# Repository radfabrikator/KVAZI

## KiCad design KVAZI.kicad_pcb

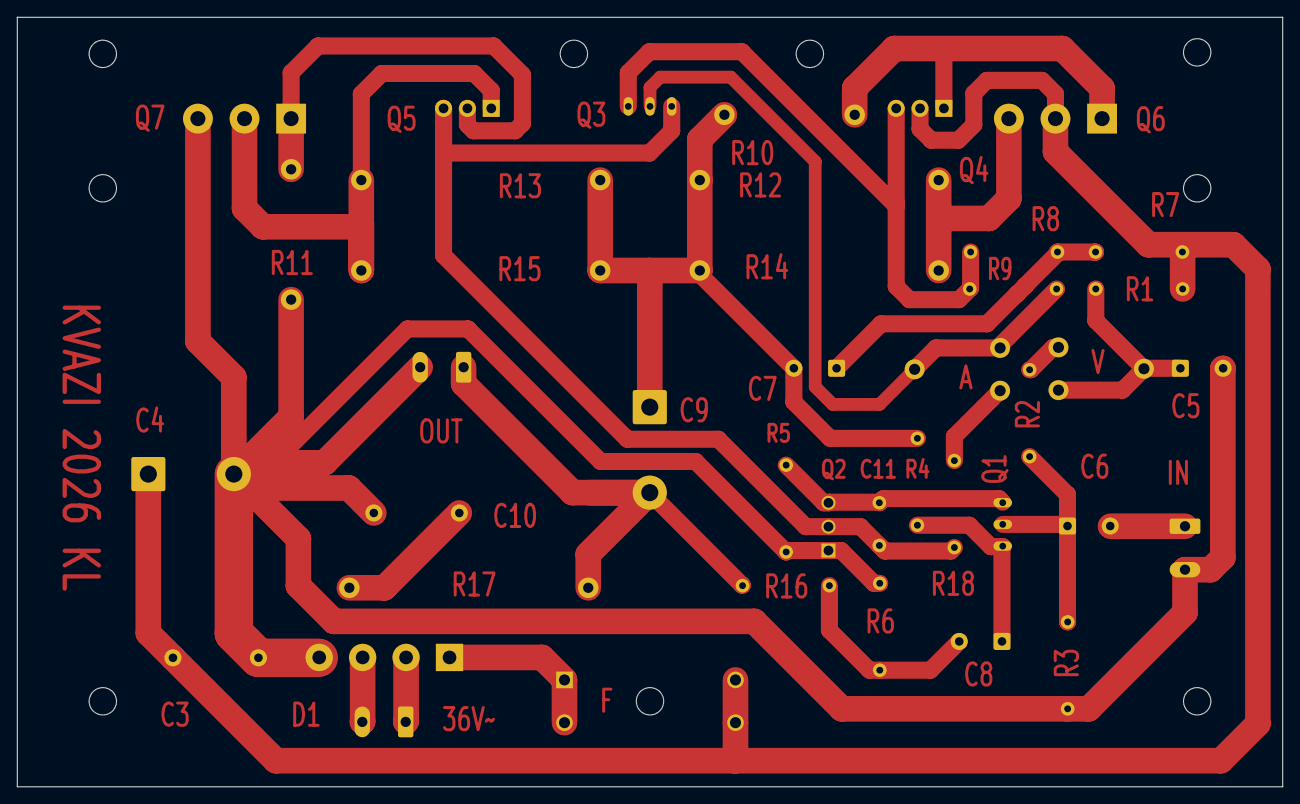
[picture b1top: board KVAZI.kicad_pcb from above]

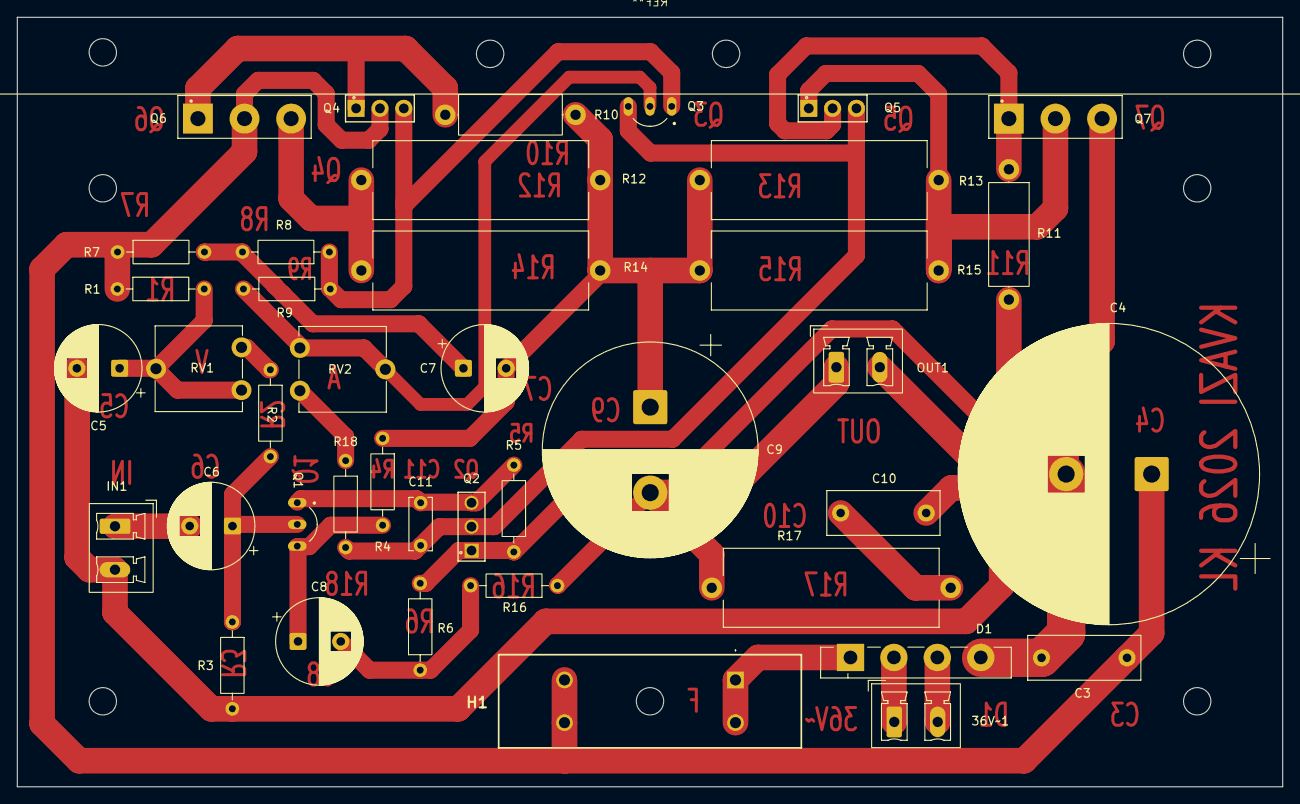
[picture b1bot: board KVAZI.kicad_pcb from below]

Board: 2 copper layers, 148.0 x 90.0 mm, 41 parts (41 on the bottom side), 24 nets.

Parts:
36V~1: Screw_Terminal_01x02; PhoenixContact_MCV_1,5_2-G-5.08_1x02_P5.08mm_Vertical
C3, C10: c=100n; C_Rect_L13.0mm_W5.0mm_P10.00mm_FKS3_FKP3_MKS4
C4: c=10000u; CP_Radial_D35.0mm_P10.00mm_SnapIn
C5: c=10u; CP_Radial_D10.0mm_P5.00mm
C6: c=2u; CP_Radial_D10.0mm_P5.00mm
C7: c=50u; CP_Radial_D10.0mm_P5.00mm
C8: c=100u; CP_Radial_D10.0mm_P5.00mm
C9: c=3300u; CP_Radial_D25.0mm_P10.00mm_SnapIn
C11: c=100p; C_Disc_D6.0mm_W2.5mm_P5.00mm
D1: GBU8D; Diode_Bridge_Vishay_GBU
H1: 0031.8231; 00318231
IN1: Screw_Terminal_01x02; PhoenixContact_MCV_1,5_2-G-5.08_1x02_P5.08mm_Vertical
OUT1: Screw_Terminal_01x02; PhoenixContact_MCV_1,5_2-G-5.08_1x02_P5.08mm_Vertical
Q1: BC556B; TO92254P460H750-3
Q2, Q4: BD139; SOT-32_STM
Q3: BC546B; TO92254P460H750-3
Q5: BD140; SOT-32_STM
Q6, Q7: TIP35C; TO545P1560X500X2445-3B
R1: r=82k; R_Axial_DIN0207_L6.3mm_D2.5mm_P10.16mm_Horizontal
R2: r=390k; R_Axial_DIN0207_L6.3mm_D2.5mm_P10.16mm_Horizontal
R3: r=470k; R_Axial_DIN0207_L6.3mm_D2.5mm_P10.16mm_Horizontal
R4, R16: r=10k; R_Axial_DIN0207_L6.3mm_D2.5mm_P10.16mm_Horizontal
R5: r=5.6k; R_Axial_DIN0207_L6.3mm_D2.5mm_P10.16mm_Horizontal
R6: r=91; R_Axial_DIN0207_L6.3mm_D2.5mm_P10.16mm_Horizontal
R7: r=330; R_Axial_DIN0207_L6.3mm_D2.5mm_P10.16mm_Horizontal
R8, R9: r=2.2k; R_Axial_DIN0207_L6.3mm_D2.5mm_P10.16mm_Horizontal
R10, R11: r=56; R_Axial_DIN0414_L11.9mm_D4.5mm_P15.24mm_Horizontal
R12, R13, R14, R15: r=1; R_Axial_Power_L25.0mm_W9.0mm_P27.94mm
R17: r=10; R_Axial_Power_L25.0mm_W9.0mm_P27.94mm
R18: r=1000; R_Axial_DIN0207_L6.3mm_D2.5mm_P10.16mm_Horizontal
RV1: 250k; Potentiometer_ACP_CA9-V10_Vertical
RV2: 1k; Potentiometer_ACP_CA9-V10_Vertical

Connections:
/U0: C7.2, C9.1, R4.1, R10.2, R12.2, R13.1, R14.2, R15.1
GND: C3.2, C4.2, C5.2, C10.2, D1.4 (-), IN1.2, OUT1.2, Q2.1 (E), Q7.3 (E), R3.2, R5.2, R6.2, R11.2
INPUT: C6.2, IN1.1
unnamed: 36V~1.1, D1.2
unnamed: 36V~1.2, D1.3
unnamed: C5.1, R1.2, RV1.2, RV1.3
unnamed: C7.1, R7.2, R8.2
unnamed: C8.2, R6.1, R16.2
unnamed: C10.1, R17.2
unnamed: D1.1 (+), H1.1, H1.2
unnamed: C6.1, Q1.2 (B), R2.2, R3.1
unnamed: C11.1, Q1.1 (C), Q2.3 (B), R5.1
unnamed: C8.1, Q1.3 (E), R4.2
unnamed: C11.2, Q2.2 (C), Q3.3 (E), Q5.3 (B), R18.2
unnamed: Q3.2 (B), R9.2, RV2.2, RV2.3
unnamed: Q3.1 (C), Q4.3 (B), R8.1, R9.1
unnamed: Q4.1 (E), Q6.1 (B), R10.1
unnamed: Q5.2 (C), Q7.1 (B), R11.1
unnamed: Q5.1 (E), Q7.2 (C), R13.2, R15.2
unnamed: Q6.3 (E), R12.1, R14.1
unnamed: R2.1, RV1.1
unnamed: R18.1, RV2.1
OUTPUT: C9.2, OUT1.1, R16.1, R17.1
VCC: C3.1, C4.1, H1.3, H1.4, Q4.2 (C), Q6.2 (C), R1.1, R7.1
